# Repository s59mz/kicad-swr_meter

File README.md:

# kicad-swr_meter
SWR Meter for HF Power Amplifier

Schematic:
[swr.pdf](swr.pdf)

BOM:
[swr.csv](swr.csv)

Gerbers:
[gerbers.zip](https://github.com/s59mz/kicad-swr_meter/raw/main/gerbers.zip)

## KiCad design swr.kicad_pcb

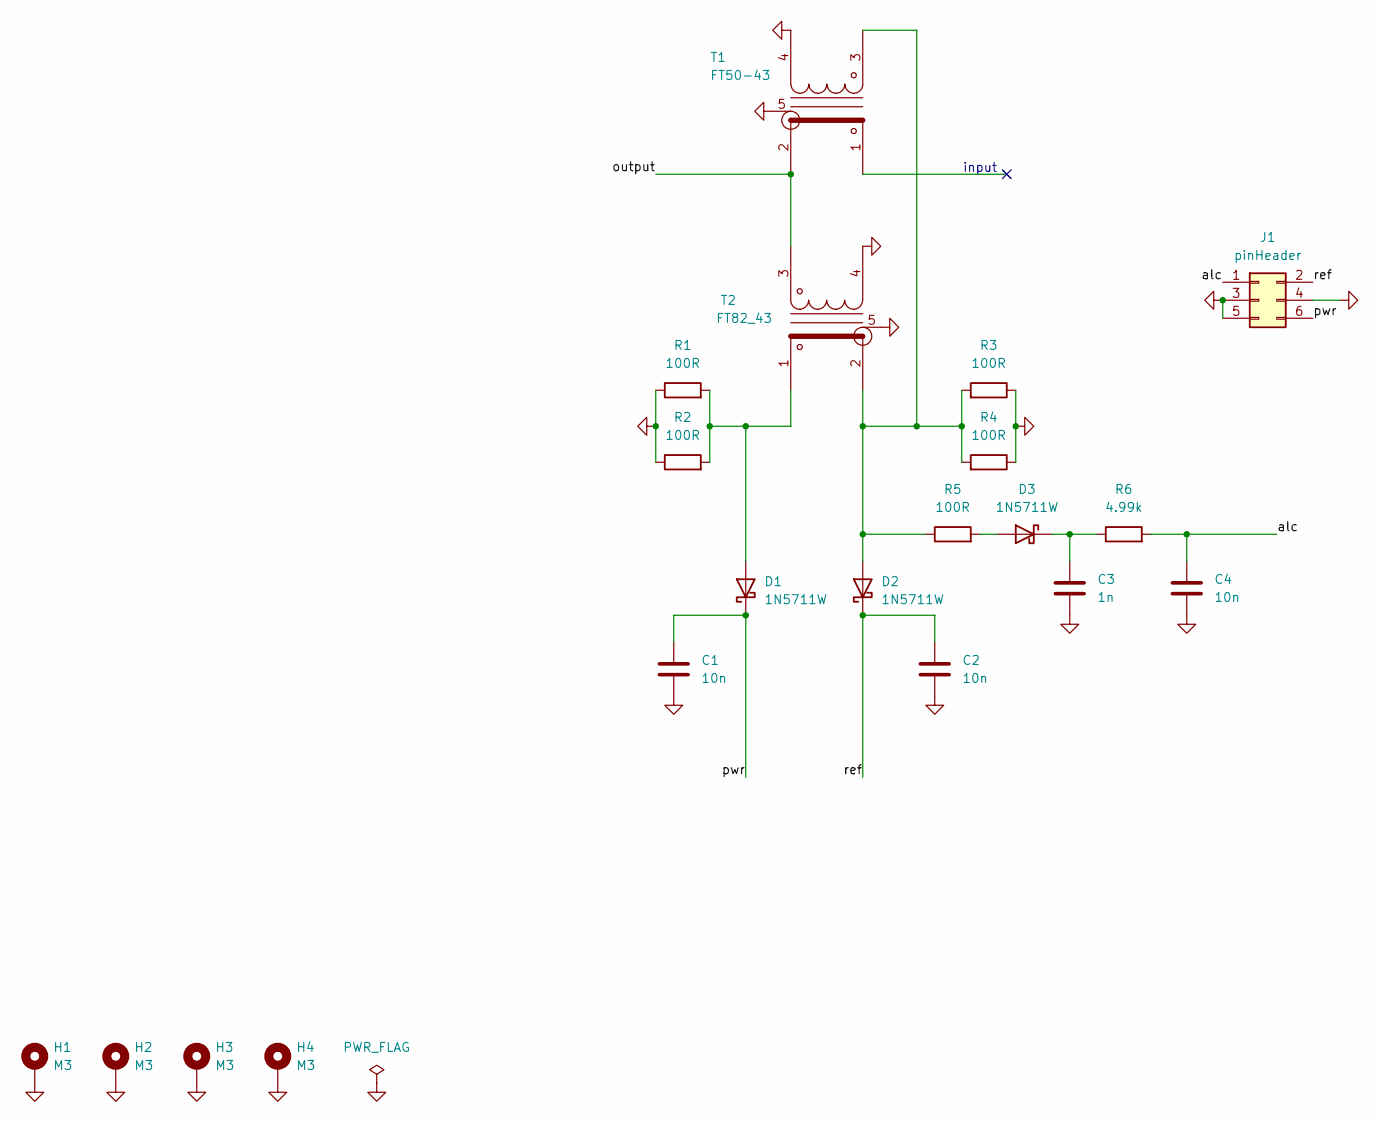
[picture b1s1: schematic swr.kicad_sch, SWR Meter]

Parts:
C1, C2, C4: 10n; C_0805_2012Metric_Pad1.18x1.45mm_HandSolder
C3: 1n; C_0805_2012Metric_Pad1.18x1.45mm_HandSolder
D1, D2, D3: 1N5711W; D_SOD-123
H1, H2, H3, H4: M3; MountingHole_3.2mm_M3_DIN965_Pad
J1: pinHeader; PinHeader_2x03_P2.54mm_Vertical
R1, R2, R3, R4: 100R; R_Axial_DIN0516_L15.5mm_D5.0mm_P20.32mm_Horizontal
R5: 100R; R_0805_2012Metric_Pad1.20x1.40mm_HandSolder
R6: 4.99k; R_0805_2012Metric_Pad1.20x1.40mm_HandSolder
T1: FT50-43; Transformer_swr_20
T2: FT82_43; Transformer_swr_25

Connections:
/alc: C4.1, J1.1, R6.2
/output: T1.2 (SA), T2.3 (AA)
/pwr: C1.1, D1.1 (K), J1.6
/ref: C2.1, D2.1 (K), J1.2
GND: C1.2, C2.2, C3.2, C4.2, H1.1, H2.1, H3.1, H4.1, J1.3, J1.4, J1.5, R1.1, R2.1, R3.1, R4.1, T1.4 (AB), T1.5 (shield), T2.4 (AB), T2.5 (shield)
unnamed: C3.1, D3.1 (K), R6.1
unnamed: D1.2 (A), R1.2, R2.2, T2.1 (SB)
unnamed: D2.2 (A), R3.2, R4.2, R5.1, T1.3 (AA), T2.2 (SA)
unnamed: D3.2 (A), R5.2

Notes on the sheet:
input

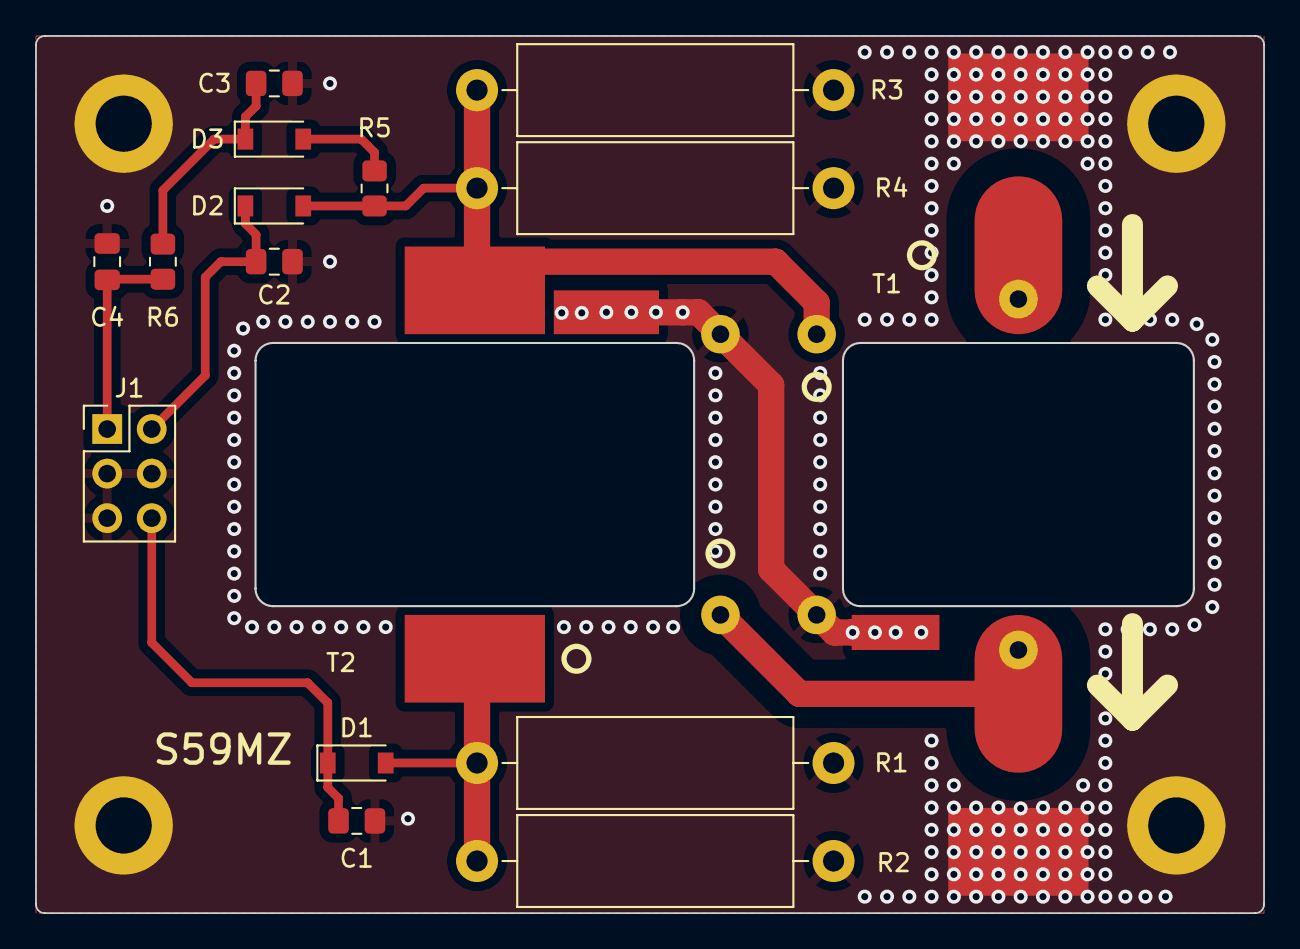
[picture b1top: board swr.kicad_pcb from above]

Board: 2 copper layers, 70.0 x 50.0 mm, 20 parts (0 on the bottom side), 9 nets.
